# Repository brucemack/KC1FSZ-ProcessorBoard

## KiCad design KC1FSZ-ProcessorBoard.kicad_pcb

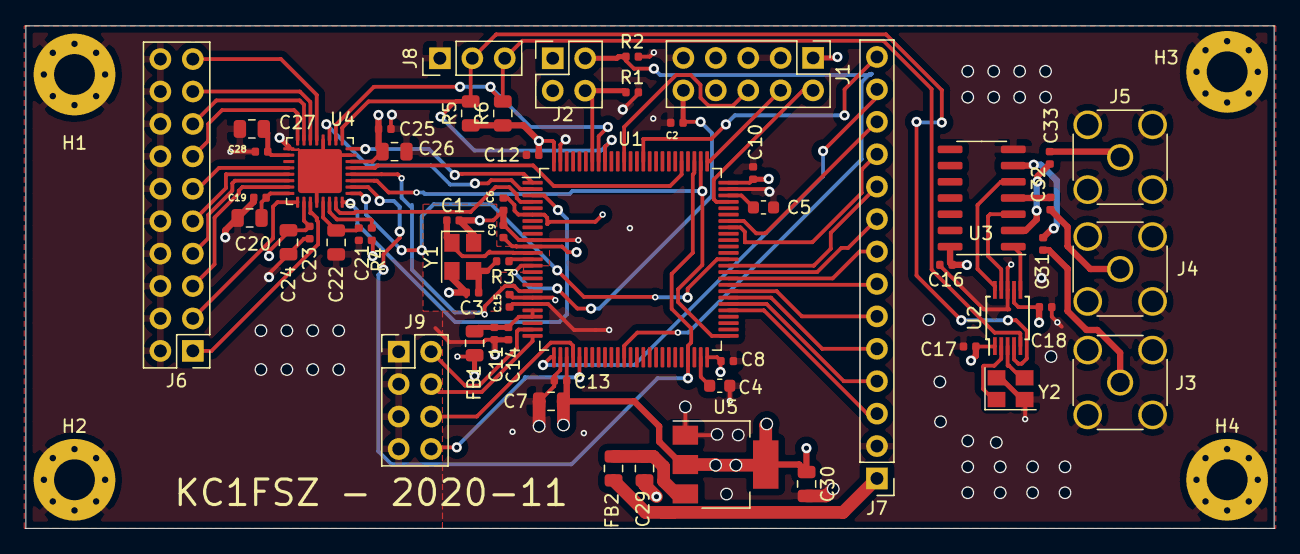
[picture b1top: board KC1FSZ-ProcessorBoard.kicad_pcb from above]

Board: 4 copper layers, 97.8 x 39.4 mm, 61 parts (0 on the bottom side), 68 nets.

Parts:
C1, C3: 12pf; C_0402_1005Metric
C2, C6, C8, C9, C10, C11, C12, C13, C15, C16, C17, C18, C19, C21, C23, C25, C28: 100nf; C_0402_1005Metric
C4, C5: 2.2uf Low ESR; C_0603_1608Metric
C7, C20, C22, C24, C26, C27, C29, C30: 10uf; C_0805_2012Metric
C14: 10nf; C_0402_1005Metric
C31, C32, C33: 100n; C_0402_1005Metric
FB1, FB2: Ferrite_Bead_Small; L_0805_2012Metric
H1, H2, H3, H4: MountingHole_Pad; MountingHole_3.2mm_M3_Pad_Via
J1: Conn_02x05_Odd_Even; PinHeader_2x05_P2.54mm_Vertical
J2: Conn_02x02_Odd_Even; PinHeader_2x02_P2.54mm_Vertical
J3, J4, J5: Conn_Coaxial; SMA_Amphenol_132134_Vertical
J6: Conn_02x10_Odd_Even; PinHeader_2x10_P2.54mm_Vertical
J7: Conn_01x14; PinHeader_1x14_P2.54mm_Vertical
J8: Conn_01x03; PinHeader_1x03_P2.54mm_Vertical
J9: Conn_02x04_Odd_Even; PinHeader_2x04_P2.54mm_Vertical
R1, R2: 10k; R_0402_1005Metric
R3: 220; R_0402_1005Metric
R4: 4.7k; R_0402_1005Metric
R5, R6: 4.7k; R_0805_2012Metric
U1: STM32F407VETx; LQFP-100_14x14mm_P0.5mm
U2: Si5351A-B-GT; MSOP-10_3x3mm_P0.5mm
U3: 74HC04; SOIC-14_3.9x8.7mm_P1.27mm
U4: TLV320AIC3204IRHBR; QFN-32-1EP_5x5mm_P0.5mm_EP3.45x3.45mm
U5: AMS1117-3.3; SOT-223-3_TabPin2
Y1: 16MHz; Crystal_SMD_3225-4Pin_3.2x2.5mm
Y2: Crystal_GND24; Crystal_SMD_3225-4Pin_3.2x2.5mm

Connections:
+3.3VA: C11.1, C14.1, FB1.1, U1.21, U1.22
+3V3: C6.1, C7.1, C8.1, C9.1, C10.1, C12.1, C13.1, C15.1, C16.1, C17.1, C18.1, C23.1, C24.1, C25.1, C26.1, C30.1, FB1.2, J1.1, J2.1, J2.3, R4.2, R5.1, R6.1, U1.6, U1.11, U1.19, U1.28, U1.50, U1.75, U1.100, U2.1, U2.7, U3.14, U4.6, U4.26, U5.2
ADC1_IN1: J9.2, U1.24
ADC1_IN2: J9.4, U1.25
BOOT0: J2.4, R1.1, U1.94
BOOT1: J2.2, R2.1, U1.37
CLK0: U2.10, U3.5
CLK1: U2.9, U3.3
CLK2: U2.6, U3.1
CODEC_MFP3: U1.1, U4.8
CODEC_MFP4: U1.2, U4.11
CODEC_MFP5: U1.3, U4.32
CODEC_RESET: U1.4, U4.31
DAC1_OUT1: J9.6, U1.29
DAC1_OUT2: J9.8, U1.30
GND: C1.2, C2.2, C3.2, C4.2, C5.2, C6.2, C7.2, C8.2, C9.2, C10.2, C11.2, C12.2, C13.2, C14.2, C15.2, C16.2, C17.2, C18.2, C19.2, C20.2, C21.2, C22.2, C23.2, C24.2, C25.2, C26.2, C27.2, C28.2, C29.2, C30.2, H1.1, H2.1, H3.1, H4.1, J1.3, J1.5, J1.9, J3.2, J4.2, J5.2, J6.2, J6.4, J6.6, J6.8, J6.10, J6.12, J6.14, J6.16, J6.18, J6.20, J7.2, J8.1, J9.1, J9.3, J9.5, J9.7, R1.2, R2.2, U1.10, U1.20, U1.27, U1.74, U1.99, U2.8, U3.7, U4.7, U4.12, U4.17, U4.28, U4.33, U5.1, Y1.2, Y1.4, Y2.2, Y2.4
GPIO_0: J7.3, U1.55
GPIO_1: J7.4, U1.56
GPIO_2: J7.5, U1.57
GPIO_3: J7.6, U1.58
GPIO_4: J7.7, U1.59
GPIO_5: J7.8, U1.60
GPIO_6: J7.9, U1.61
GPIO_7: J7.10, U1.62
HPL: J6.3, U4.25
HPR: J6.1, U4.27
HSE_IN: C1.1, U1.12, Y1.1
HSE_OUT: R3.1, U1.13
I2C1_SCL: J8.2, R5.2, U1.92, U2.4, U4.9
I2C1_SDA: J8.3, R6.2, U1.93, U2.5, U4.10
I2S2_CK: U1.47, U1.78, U4.2
I2S2_MCK: U1.63, U4.1
I2S2_SD: U1.18, U4.4
I2S2_WS: U1.51, U1.77, U4.3
I2S3_SD: U1.80, U4.5
IN1_L: J6.19, U4.13
IN1_R: J6.17, U4.14
IN2_L: J6.15, U4.15
IN2_R: J6.13, U4.16
IN3_L: J6.11, U4.20
IN3_R: J6.9, U4.21
LOL: J6.7, U4.22
LOR: J6.5, U4.23
NRST: C2.1, J1.10, U1.14
unnamed: C3.1, R3.2, Y1.3
unnamed: C4.1, U1.49
unnamed: C5.1, U1.73
unnamed: C19.1, C20.1, U4.24
unnamed: C21.1, C22.1, U4.29
unnamed: C27.1, C28.1, U4.18
unnamed: C29.1, FB2.1, U5.3
unnamed: C31.1, U3.6
unnamed: C32.1, U3.4
unnamed: C33.1, U3.2
unnamed: R4.1, U4.30
unnamed: U2.2, Y2.1
unnamed: U2.3, Y2.3
PWR: FB2.2, J7.1
SWCLK: J1.4, U1.76
SWDIO: J1.2, U1.72
SWO: J1.6, U1.89
USART1_RX: J7.12, U1.69
USART1_TX: J7.11, U1.68
USART2_RX: J7.13, U1.26
USART2_TX: J7.14, U1.86
~CLK0: C31.2, J3.1
~CLK1: C32.2, J4.1
~CLK2: C33.2, J5.1
